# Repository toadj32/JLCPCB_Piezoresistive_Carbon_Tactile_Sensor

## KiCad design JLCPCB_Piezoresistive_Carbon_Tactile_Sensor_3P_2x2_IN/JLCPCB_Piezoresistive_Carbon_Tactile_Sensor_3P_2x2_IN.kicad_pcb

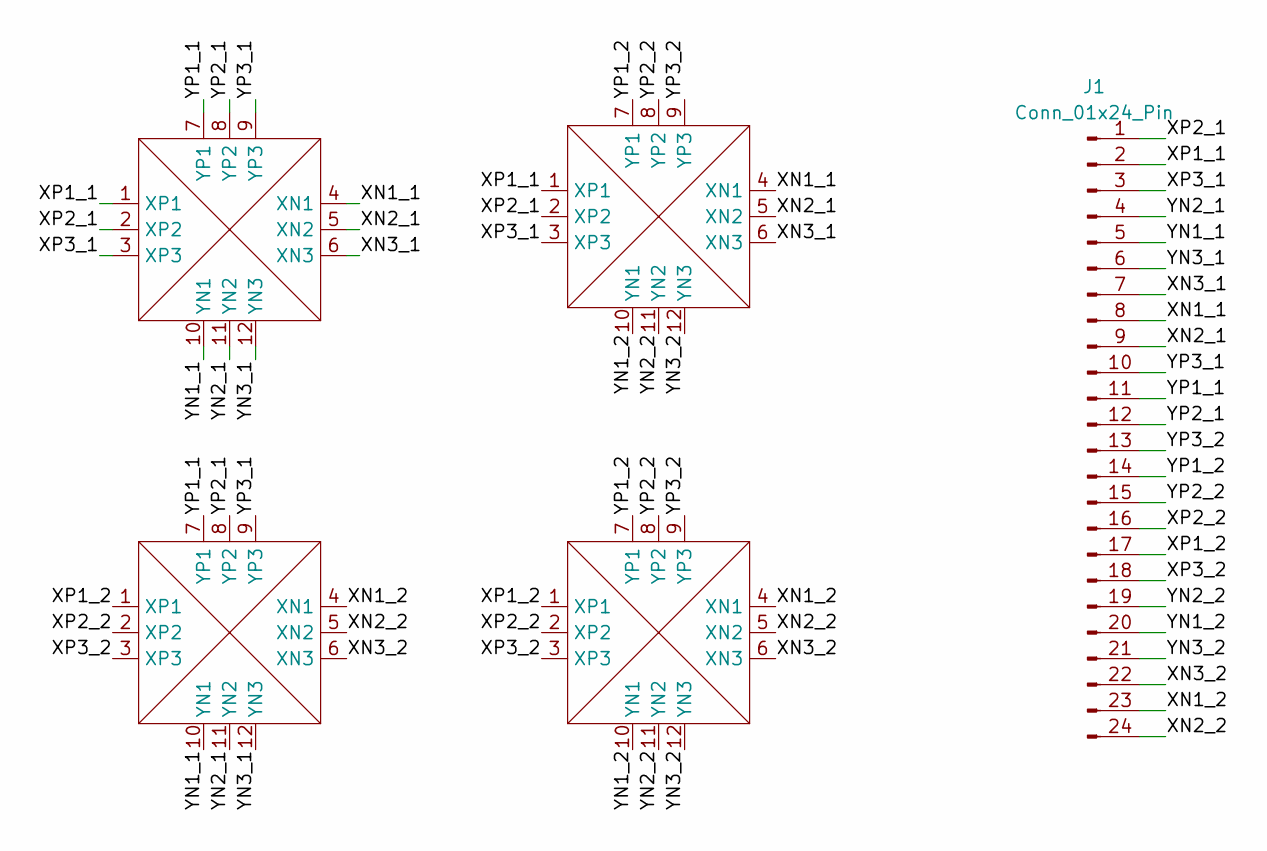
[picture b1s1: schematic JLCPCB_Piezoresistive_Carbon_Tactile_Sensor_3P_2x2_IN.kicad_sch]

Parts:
J1: Conn_01x24_Pin; PinHeader_1x24_P1.00mm_Vertical
T1, T2, T3, T4: Taxel_Pyramid_3P; Pyrmd_taxel_3P_IN

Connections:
/XN1_1: J1.8, T1.4 (XN1), T2.4 (XN1)
/XN1_2: J1.23, T3.4 (XN1), T4.4 (XN1)
/XN2_1: J1.9, T1.5 (XN2), T2.5 (XN2)
/XN2_2: J1.24, T3.5 (XN2), T4.5 (XN2)
/XN3_1: J1.7, T1.6 (XN3), T2.6 (XN3)
/XN3_2: J1.22, T3.6 (XN3), T4.6 (XN3)
/XP1_1: J1.2, T1.1 (XP1), T2.1 (XP1)
/XP1_2: J1.17, T3.1 (XP1), T4.1 (XP1)
/XP2_1: J1.1, T1.2 (XP2), T2.2 (XP2)
/XP2_2: J1.16, T3.2 (XP2), T4.2 (XP2)
/XP3_1: J1.3, T1.3 (XP3), T2.3 (XP3)
/XP3_2: J1.18, T3.3 (XP3), T4.3 (XP3)
/YN1_1: J1.5, T1.10 (YN1), T4.10 (YN1)
/YN1_2: J1.20, T2.10 (YN1), T3.10 (YN1)
/YN2_1: J1.4, T1.11 (YN2), T4.11 (YN2)
/YN2_2: J1.19, T2.11 (YN2), T3.11 (YN2)
/YN3_1: J1.6, T1.12 (YN3), T4.12 (YN3)
/YN3_2: J1.21, T2.12 (YN3), T3.12 (YN3)
/YP1_1: J1.11, T1.7 (YP1), T4.7 (YP1)
/YP1_2: J1.14, T2.7 (YP1), T3.7 (YP1)
/YP2_1: J1.12, T1.8 (YP2), T4.8 (YP2)
/YP2_2: J1.15, T2.8 (YP2), T3.8 (YP2)
/YP3_1: J1.10, T1.9 (YP3), T4.9 (YP3)
/YP3_2: J1.13, T2.9 (YP3), T3.9 (YP3)

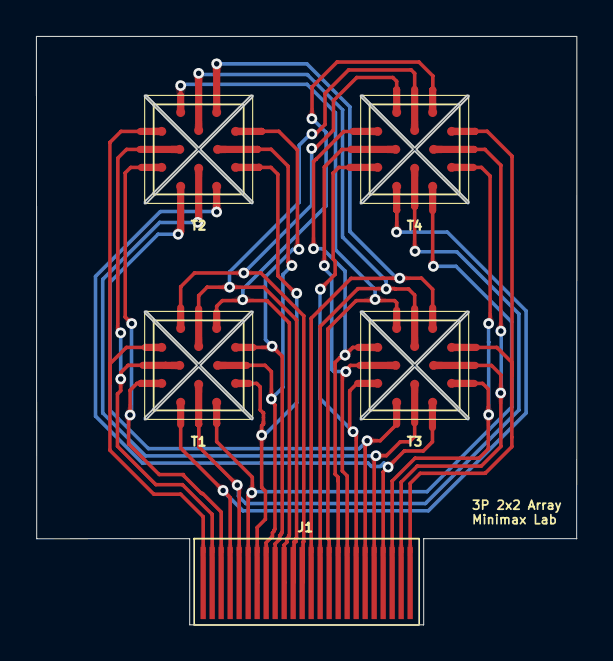
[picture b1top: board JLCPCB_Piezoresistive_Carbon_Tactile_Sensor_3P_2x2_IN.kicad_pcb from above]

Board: 2 copper layers, 30.0 x 32.7 mm, 5 parts (0 on the bottom side), 24 nets.

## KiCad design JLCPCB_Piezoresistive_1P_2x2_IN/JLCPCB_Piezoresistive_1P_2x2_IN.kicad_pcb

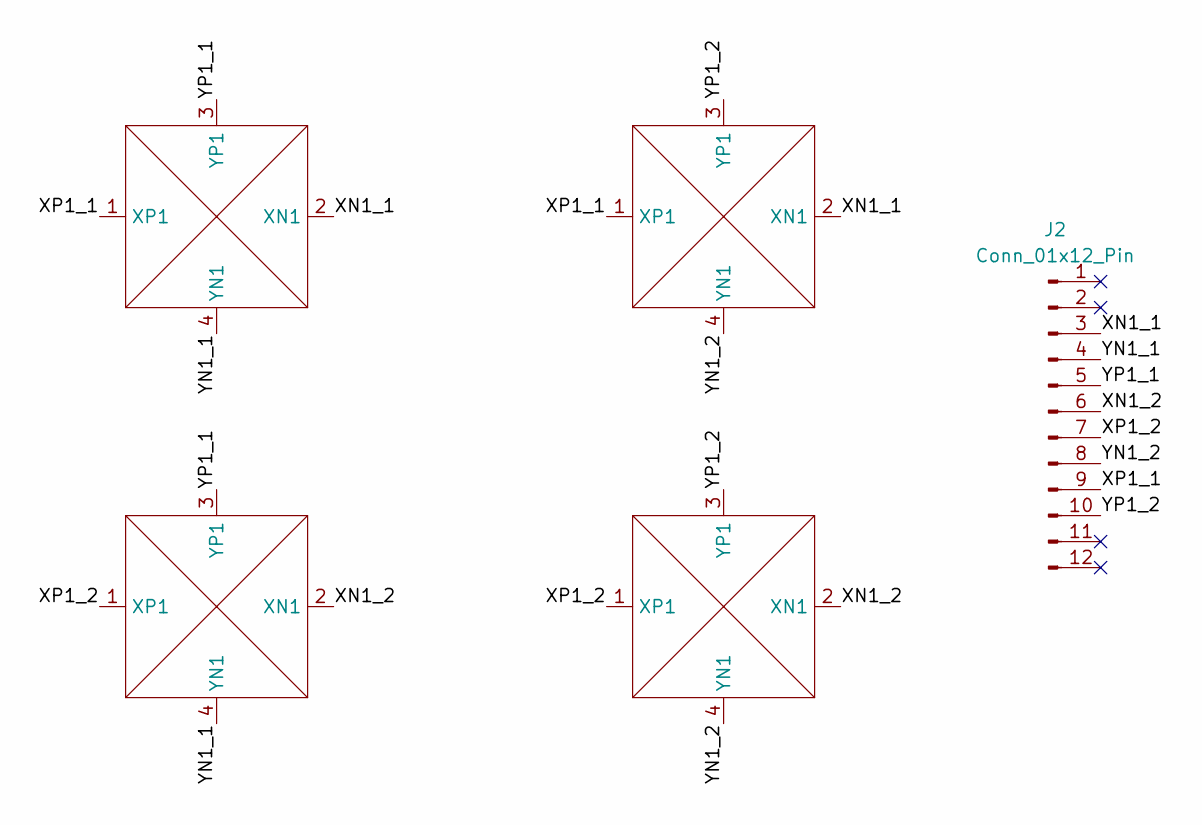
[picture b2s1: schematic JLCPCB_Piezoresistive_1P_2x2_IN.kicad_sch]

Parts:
J2: Conn_01x12_Pin; FFC_12P_0.5MM
T1, T2, T3, T4: Taxel_Pyramid_1P; Pyrmd_Taxel_1P_IN

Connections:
/XN1_1: J2.3, T1.2 (XN1), T2.2 (XN1)
/XN1_2: J2.6, T3.2 (XN1), T4.2 (XN1)
/XP1_1: J2.9, T1.1 (XP1), T2.1 (XP1)
/XP1_2: J2.7, T3.1 (XP1), T4.1 (XP1)
/YN1_1: J2.4, T1.4 (YN1), T3.4 (YN1)
/YN1_2: J2.8, T2.4 (YN1), T4.4 (YN1)
/YP1_1: J2.5, T1.3 (YP1), T3.3 (YP1)
/YP1_2: J2.10, T2.3 (YP1), T4.3 (YP1)

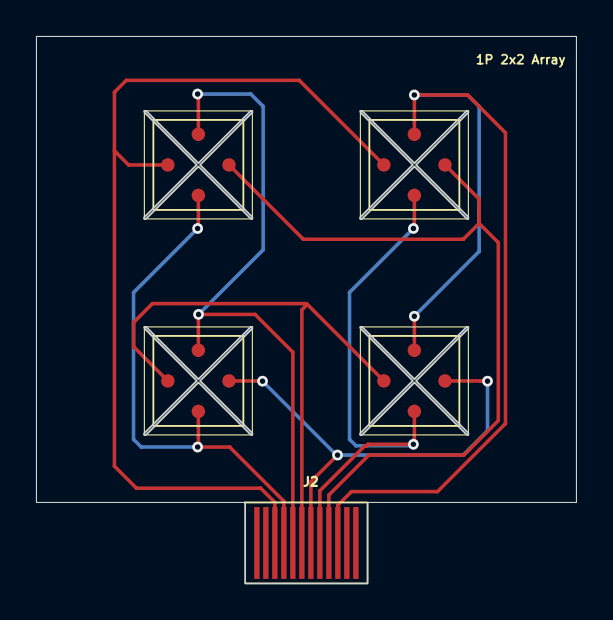
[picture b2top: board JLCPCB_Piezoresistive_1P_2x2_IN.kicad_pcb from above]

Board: 2 copper layers, 30.0 x 30.4 mm, 5 parts (0 on the bottom side), 8 nets.

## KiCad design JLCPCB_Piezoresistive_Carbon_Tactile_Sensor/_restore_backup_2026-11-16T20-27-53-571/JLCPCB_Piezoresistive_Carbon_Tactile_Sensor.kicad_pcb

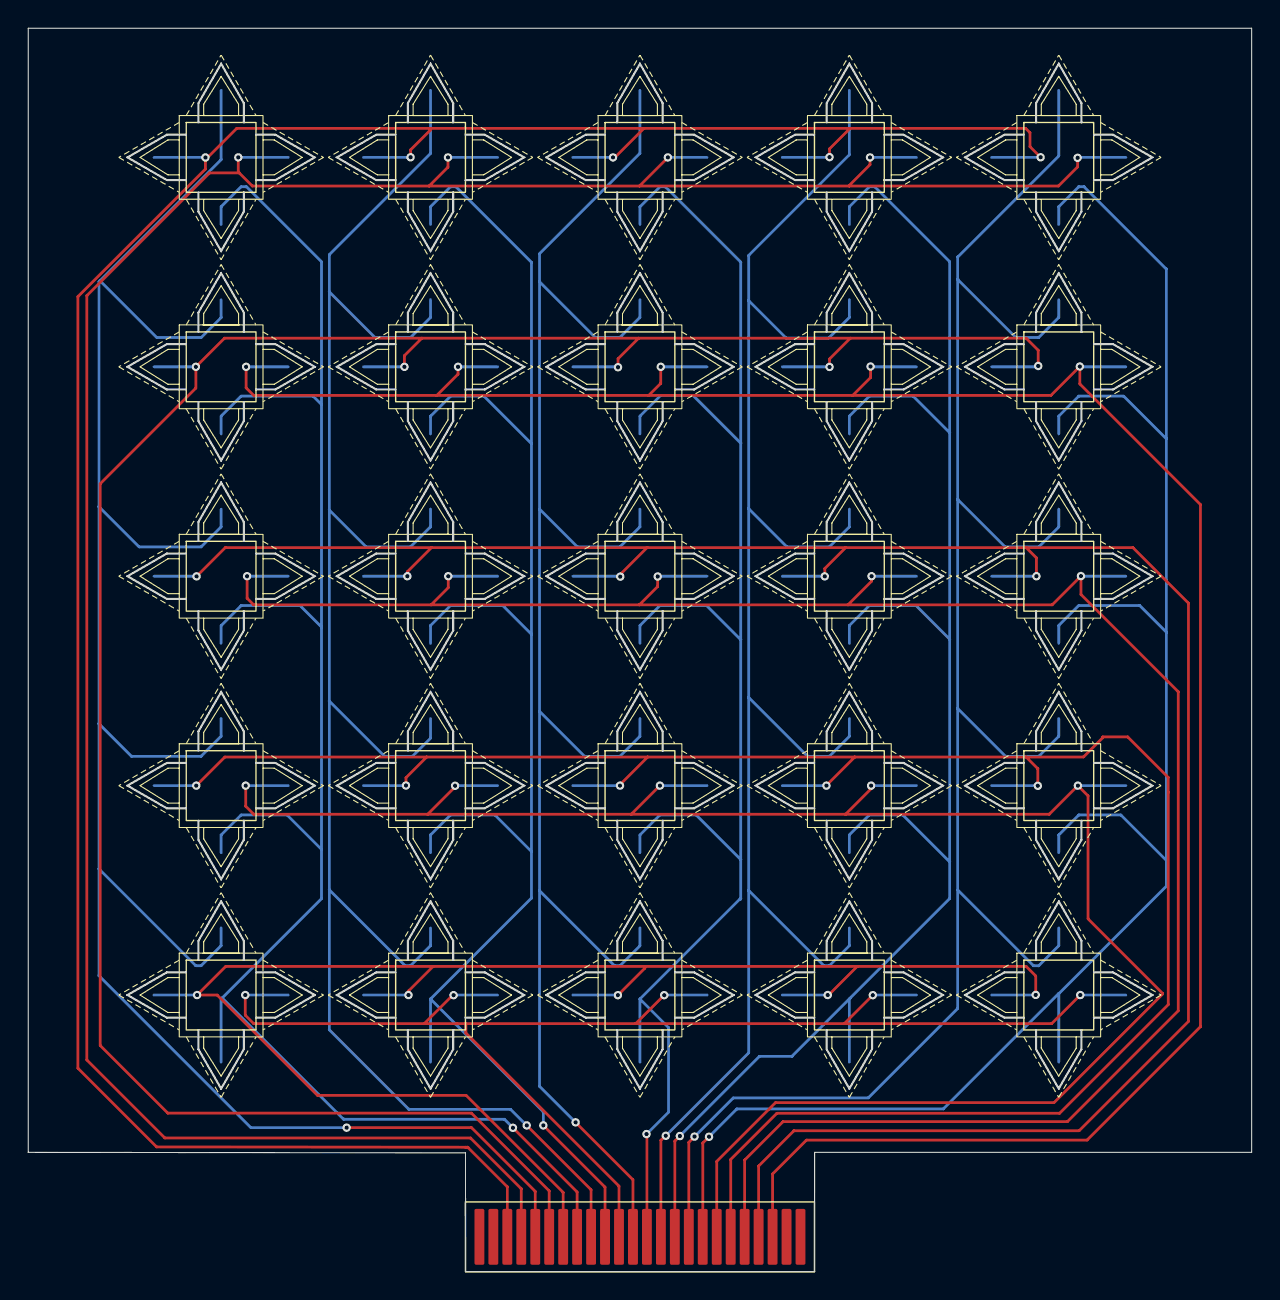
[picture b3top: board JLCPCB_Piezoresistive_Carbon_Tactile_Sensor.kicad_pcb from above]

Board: 2 copper layers, 87.6 x 89.1 mm, 26 parts (0 on the bottom side), 20 nets.

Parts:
J2: Conn_01x24_Pin; FPC_Tail_24P_P1.0
T1, T2, T3, T4, T5, T6, T7, T8, T9, T10, T11, T12, T13, T14, T15, T16, T17, T18, T19, T20, T21, T22, T23, T24, T25: Taxel_Pyramid; Taxel_Faces_Out

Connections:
/XN_R1: J2.3, T1.2 (XN), T2.2 (XN), T3.2 (XN), T4.2 (XN), T5.2 (XN)
/XN_R2: J2.6, T6.2 (XN), T7.2 (XN), T8.2 (XN), T9.2 (XN), T10.2 (XN)
/XN_R3: J2.21, T11.2 (XN), T12.2 (XN), T13.2 (XN), T14.2 (XN), T15.2 (XN)
/XN_R4: J2.19, T16.2 (XN), T17.2 (XN), T18.2 (XN), T19.2 (XN), T20.2 (XN)
/XN_R5: J2.7, T21.2 (XN), T22.2 (XN), T23.2 (XN), T24.2 (XN), T25.2 (XN)
/XP_R1: J2.4, T1.1 (XP), T2.1 (XP), T3.1 (XP), T4.1 (XP), T5.1 (XP)
/XP_R2: J2.22, T6.1 (XP), T7.1 (XP), T8.1 (XP), T9.1 (XP), T10.1 (XP)
/XP_R3: J2.20, T11.1 (XP), T12.1 (XP), T13.1 (XP), T14.1 (XP), T15.1 (XP)
/XP_R4: J2.18, T16.1 (XP), T17.1 (XP), T18.1 (XP), T19.1 (XP), T20.1 (XP)
/XP_R5: J2.11, T21.1 (XP), T22.1 (XP), T23.1 (XP), T24.1 (XP), T25.1 (XP)
/YN_C1: J2.8, T1.4 (YN), T6.4 (YN), T11.4 (YN), T16.4 (YN), T21.4 (YN)
/YN_C2: J2.10, T2.4 (YN), T7.4 (YN), T12.4 (YN), T17.4 (YN), T22.4 (YN)
/YN_C3: J2.13, T3.4 (YN), T8.4 (YN), T13.4 (YN), T18.4 (YN), T23.4 (YN)
/YN_C4: J2.15, T4.4 (YN), T9.4 (YN), T14.4 (YN), T19.4 (YN), T24.4 (YN)
/YN_C5: J2.17, T5.4 (YN), T10.4 (YN), T15.4 (YN), T20.4 (YN), T25.4 (YN)
/YP_C1: J2.5, T1.3 (YP), T6.3 (YP), T11.3 (YP), T16.3 (YP), T21.3 (YP)
/YP_C2: J2.9, T2.3 (YP), T7.3 (YP), T12.3 (YP), T17.3 (YP), T22.3 (YP)
/YP_C3: J2.12, T3.3 (YP), T8.3 (YP), T13.3 (YP), T18.3 (YP), T23.3 (YP)
/YP_C4: J2.14, T4.3 (YP), T9.3 (YP), T14.3 (YP), T19.3 (YP), T24.3 (YP)
/YP_C5: J2.16, T5.3 (YP), T10.3 (YP), T15.3 (YP), T20.3 (YP), T25.3 (YP)
